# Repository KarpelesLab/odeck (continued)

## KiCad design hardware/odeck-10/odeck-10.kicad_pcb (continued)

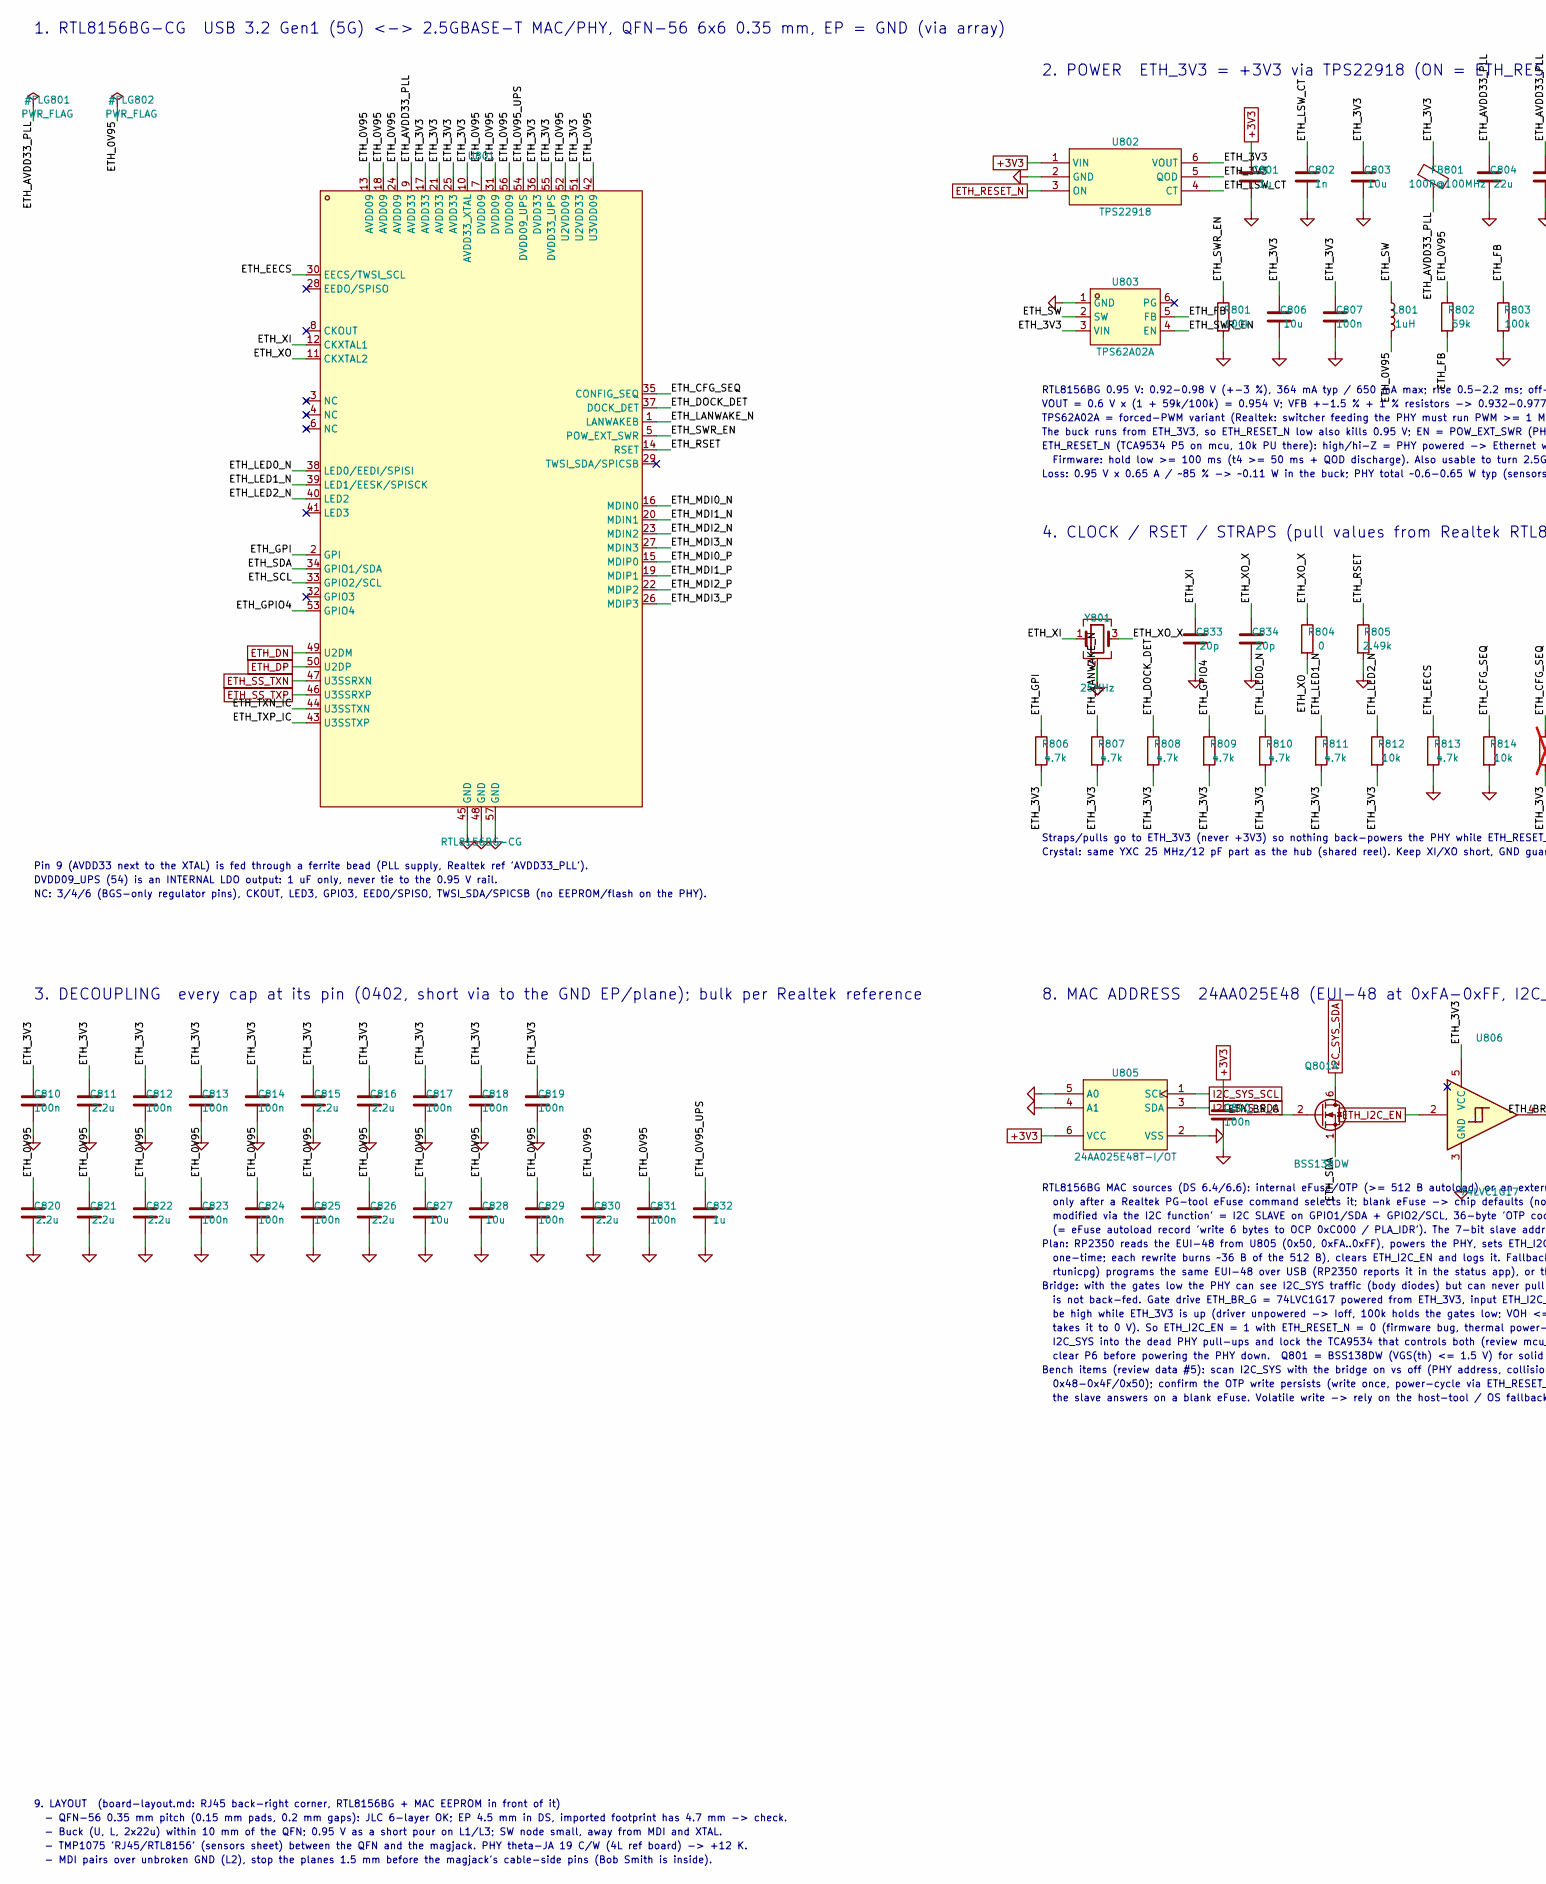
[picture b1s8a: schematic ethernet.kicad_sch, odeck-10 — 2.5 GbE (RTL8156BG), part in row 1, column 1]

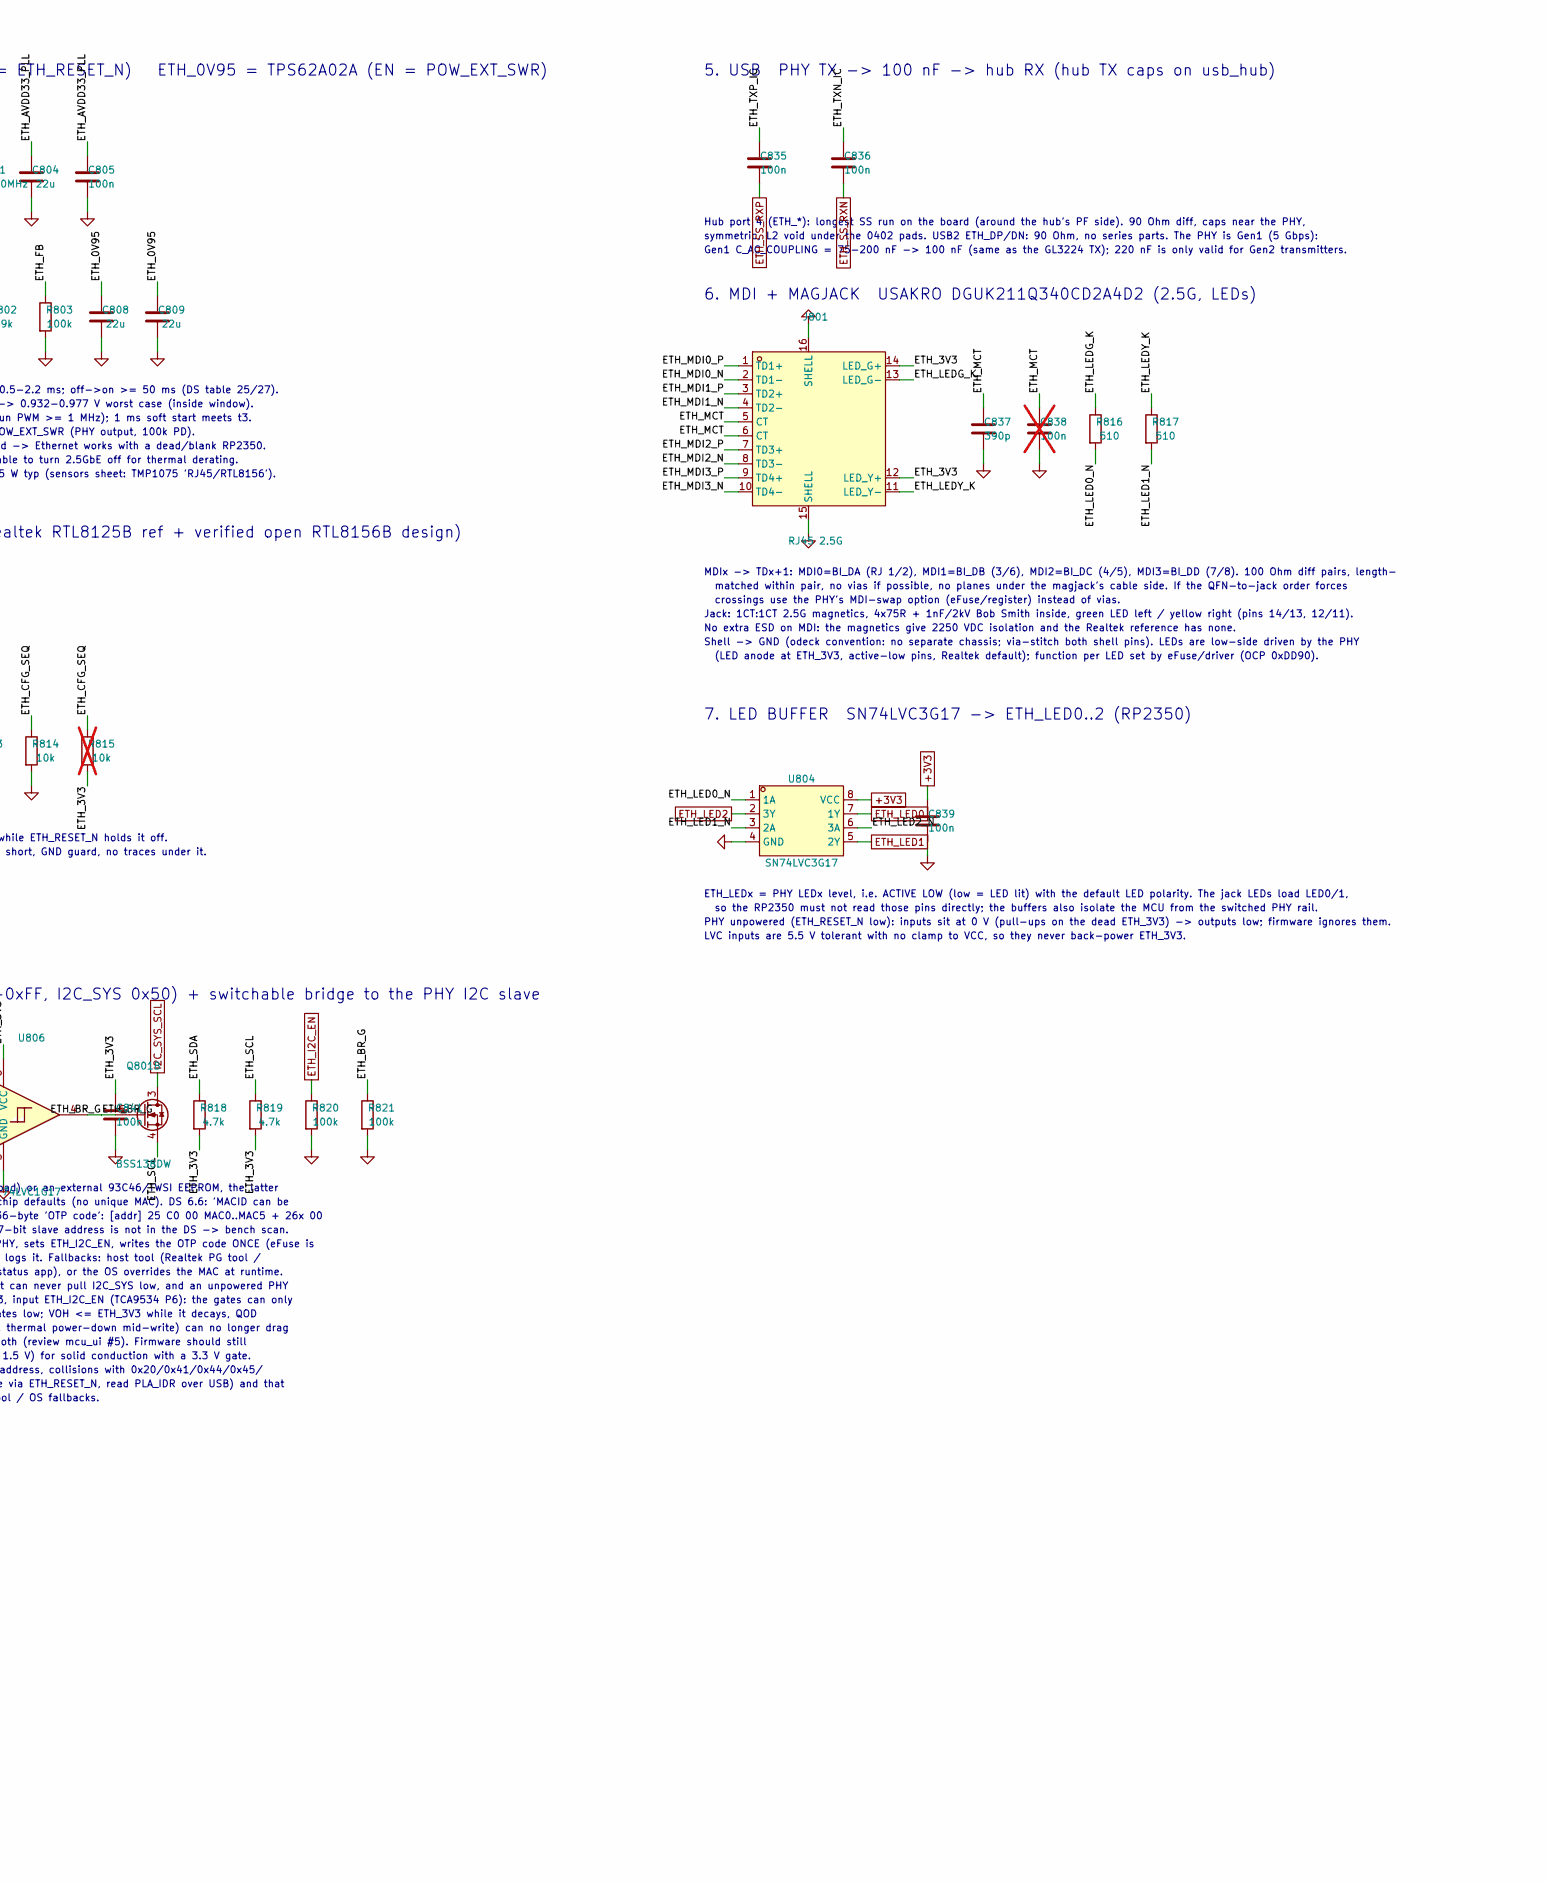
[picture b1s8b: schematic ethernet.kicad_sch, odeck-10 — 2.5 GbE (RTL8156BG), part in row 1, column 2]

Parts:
C801, C832: 1u; C_0402_1005Metric; LCSC C52923
C802: 1n; C_0402_1005Metric; LCSC C1523
C803, C806, C827, C828: 10u; C_0603_1608Metric; LCSC C19702
C804, C808, C809: 22u; C_0603_1608Metric; LCSC C59461
C805, C807, C810, C812, C813, C814, C817, C818, C819, C823, C824, C825, C829, C831, C835, C836, C839, C840, C841: 100n; C_0402_1005Metric; LCSC C1525
C811, C815, C816, C820, C821, C822, C826, C830: 2.2u; C_0402_1005Metric; LCSC C12530
C833, C834: 20p; C_0402_1005Metric; LCSC C1554
C837: 390p; C_0402_1005Metric; LCSC C282239
C838: 100n; C_0402_1005Metric; LCSC C1525; not fitted
FB801: 100R@100MHz; L_0805_2012Metric; LCSC C1015
J801: RJ45 2.5G; RJ45-TH_DGUK211Q340CD2A4D2; MPN DGUK211Q340CD2A4D2(2.5G); LCSC C19725134
L801: 1uH; L_Sunlord_SWPA4018S; LCSC C91250
Q801: BSS138DW; SOT-363_SC-70-6; MPN BSS138DW-7-F; LCSC C154900
R801, R803, R820, R821: 100k; R_0402_1005Metric; LCSC C25741
R802: 59k; R_0402_1005Metric; LCSC C32297
R804: 0; R_0402_1005Metric; LCSC C17168
R805: 2.49k; R_0402_1005Metric; LCSC C25884
R806, R807, R808, R809, R810, R811, R813, R818, R819: 4.7k; R_0402_1005Metric; LCSC C25900
R812, R814: 10k; R_0402_1005Metric; LCSC C25744
R815: 10k; R_0402_1005Metric; LCSC C25744; not fitted
R816, R817: 510; R_0402_1005Metric; LCSC C25123
U801: RTL8156BG-CG; QFN-56_L6.0-W6.0-P0.35--TL-EP4.7; MPN RTL8156BG-CG; LCSC C41376388
U802: TPS22918; SOT-23-6; MPN TPS22918DBVR; LCSC C131941
U803: TPS62A02A; SOT-5X3-6_W1.6-L1.2-P0.50-LS1.6-BL; MPN TPS62A02ADRLR; LCSC C5820994
U804: SN74LVC3G17; VSSOP-8_L2.1-W2.4-P0.50-LS3.2-BR; MPN SN74LVC3G17DCUR; LCSC C68245
U805: 24AA025E48T-I/OT; SOT-23-6; MPN 24AA025E48T-I/OT; LCSC C129895
U806: 74LVC1G17; SOT-23-5; MPN 74LVC1G17W5-7; LCSC C151394
Y801: 25MHz; Crystal_SMD_3225-4Pin_3.2x2.5mm; LCSC C9006

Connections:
+3V3: C801.1, C839.1, C840.1, U802.1 (VIN), U804.8 (VCC), U805.6 (VCC); also elsewhere on the board
/Ethernet/ETH_0V95: C808.1, C809.1, C820.1, C821.1, C822.1, C823.1, C824.1, C825.1, C826.1, C827.1, C828.1, C829.1, C830.1, C831.1, L801.2, R802.1, U801.7 (DVDD09), U801.13 (AVDD09), U801.18 (AVDD09), U801.24 (AVDD09), U801.31 (DVDD09), U801.42 (U3VDD09), U801.52 (U2VDD09), U801.56 (DVDD09)
/Ethernet/ETH_0V95_UPS: C832.1, U801.54 (DVDD09_UPS)
/Ethernet/ETH_3V3: C803.1, C806.1, C807.1, C810.1, C811.1, C812.1, C813.1, C814.1, C815.1, C816.1, C817.1, C818.1, C819.1, C841.1, FB801.1, J801.12 (LED_Y+), J801.14 (LED_G+), R806.2, R807.2, R808.2, R809.2, R810.2, R811.2, R812.2, R815.2, R818.2, R819.2, U801.10 (AVDD33_XTAL), U801.17 (AVDD33), U801.21 (AVDD33), U801.25 (AVDD33), U801.36 (DVDD33), U801.51 (U2VDD33), U801.55 (DVDD33_UPS), U802.5 (QOD), U802.6 (VOUT), U803.3 (VIN), U806.5 (VCC)
/Ethernet/ETH_AVDD33_PLL: C804.1, C805.1, FB801.2, U801.9 (AVDD33)
/Ethernet/ETH_BR_G: Q801.2 (G), Q801.5 (G), R821.1, U806.4
/Ethernet/ETH_CFG_SEQ: R814.1, R815.1, U801.35 (CONFIG_SEQ)
/Ethernet/ETH_DOCK_DET: R808.1, U801.37 (DOCK_DET)
/Ethernet/ETH_EECS: R813.1, U801.30 (EECS/TWSI_SCL)
/Ethernet/ETH_FB: R802.2, R803.1, U803.5 (FB)
/Ethernet/ETH_GPI: R806.1, U801.2 (GPI)
/Ethernet/ETH_GPIO4: R809.1, U801.53 (GPIO4)
/Ethernet/ETH_LANWAKE_N: R807.1, U801.1 (LANWAKEB)
/Ethernet/ETH_LED0_N: R810.1, R816.2, U801.38 (LED0/EEDI/SPISI), U804.1 (1A)
/Ethernet/ETH_LED1_N: R811.1, R817.2, U801.39 (LED1/EESK/SPISCK), U804.3 (2A)
/Ethernet/ETH_LED2_N: R812.1, U801.40 (LED2), U804.6 (3A)
/Ethernet/ETH_LEDG_K: J801.13 (LED_G-), R816.1
/Ethernet/ETH_LEDY_K: J801.11 (LED_Y-), R817.1
/Ethernet/ETH_LSW_CT: C802.1, U802.4 (CT)
/Ethernet/ETH_MCT: C837.1, C838.1, J801.5 (CT), J801.6 (CT)
/Ethernet/ETH_MDI0_N: J801.2 (TD1-), U801.16 (MDIN0)
/Ethernet/ETH_MDI0_P: J801.1 (TD1+), U801.15 (MDIP0)
/Ethernet/ETH_MDI1_N: J801.4 (TD2-), U801.20 (MDIN1)
/Ethernet/ETH_MDI1_P: J801.3 (TD2+), U801.19 (MDIP1)
/Ethernet/ETH_MDI2_N: J801.8 (TD3-), U801.23 (MDIN2)
/Ethernet/ETH_MDI2_P: J801.7 (TD3+), U801.22 (MDIP2)
/Ethernet/ETH_MDI3_N: J801.10 (TD4-), U801.27 (MDIN3)
/Ethernet/ETH_MDI3_P: J801.9 (TD4+), U801.26 (MDIP3)
/Ethernet/ETH_RSET: R805.1, U801.14 (RSET)
/Ethernet/ETH_SCL: Q801.4 (S), R819.1, U801.33 (GPIO2/SCL)
/Ethernet/ETH_SDA: Q801.1 (S), R818.1, U801.34 (GPIO1/SDA)
/Ethernet/ETH_SW: L801.1, U803.2 (SW)
/Ethernet/ETH_SWR_EN: R801.1, U801.5 (POW_EXT_SWR), U803.4 (EN)
/Ethernet/ETH_TXN_IC: C836.1, U801.44 (U3SSTXN)
/Ethernet/ETH_TXP_IC: C835.1, U801.43 (U3SSTXP)
/Ethernet/ETH_XI: C833.1, U801.12 (CKXTAL1), Y801.1
/Ethernet/ETH_XO: R804.2, U801.11 (CKXTAL2)
/Ethernet/ETH_XO_X: C834.1, R804.1, Y801.3
ETH_DN: U801.49 (U2DM); also elsewhere on the board
ETH_DP: U801.50 (U2DP); also elsewhere on the board
ETH_I2C_EN: R820.1, U806.2; also elsewhere on the board
ETH_LED0: U804.7 (1Y); also elsewhere on the board
ETH_LED1: U804.5 (2Y); also elsewhere on the board
ETH_LED2: U804.2 (3Y); also elsewhere on the board
ETH_RESET_N: U802.3 (ON); also elsewhere on the board
ETH_SS_RXN: C836.2; also elsewhere on the board
ETH_SS_RXP: C835.2; also elsewhere on the board
ETH_SS_TXN: U801.47 (U3SSRXN); also elsewhere on the board
ETH_SS_TXP: U801.46 (U3SSRXP); also elsewhere on the board
GND: C801.2, C802.2, C803.2, C804.2, C805.2, C806.2, C807.2, C808.2, C809.2, C810.2, C811.2, C812.2, C813.2, C814.2, C815.2, C816.2, C817.2, C818.2, C819.2, C820.2, C821.2, C822.2, C823.2, C824.2, C825.2, C826.2, C827.2, C828.2, C829.2, C830.2, C831.2, C832.2, C833.2, C834.2, C837.2, C838.2, C839.2, C840.2, C841.2, J801.15 (SHELL), J801.16 (SHELL), R801.2, R803.2, R805.2, R813.2, R814.2, R820.2, R821.2, U801.45 (GND), U801.48 (GND), U801.57 (GND), U802.2 (GND), U803.1 (GND), U804.4 (GND), U805.2 (VSS), U805.4 (A1), U805.5 (A0), U806.3 (GND), Y801.2 (G), Y801.4 (G); also elsewhere on the board
I2C_SYS_SCL: Q801.3 (D), U805.1 (SCL); also elsewhere on the board
I2C_SYS_SDA: Q801.6 (D), U805.3 (SDA); also elsewhere on the board

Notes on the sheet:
1. RTL8156BG-CG USB 3.2 Gen1 (5G) <-> 2.5GBASE-T MAC/PHY, QFN-56 6x6 0.35 mm, EP = GND (via array)
Pin 9 (AVDD33 next to the XTAL) is fed through a ferrite bead (PLL supply, Realtek ref 'AVDD33_PLL').
DVDD09_UPS (54) is an INTERNAL LDO output: 1 uF only, never tie to the 0.95 V rail.
NC: 3/4/6 (BGS-only regulator pins), CKOUT, LED3, GPIO3, EEDO/SPISO, TWSI_SDA/SPICSB (no EEPROM/flash on the PHY).
2. POWER ETH_3V3 = +3V3 via TPS22918 (ON = ETH_RESET_N) ETH_0V95 = TPS62A02A (EN = POW_EXT_SWR)
RTL8156BG 0.95 V: 0.92-0.98 V (+-3 %), 364 mA typ / 650 mA max; rise 0.5-2.2 ms; off->on >= 50 ms (DS table 25/27).
VOUT = 0.6 V x (1 + 59k/100k) = 0.954 V; VFB +-1.5 % + 1 % resistors -> 0.932-0.977 V worst case (inside window).
TPS62A02A = forced-PWM variant (Realtek: switcher feeding the PHY must run PWM >= 1 MHz); 1 ms soft start meets t3.
The buck runs from ETH_3V3, so ETH_RESET_N low also kills 0.95 V; EN = POW_EXT_SWR (PHY output, 100k PD).
ETH_RESET_N (TCA9534 P5 on mcu, 10k PU there): high/hi-Z = PHY powered -> Ethernet works with a dead/blank RP2350.
Firmware: hold low >= 100 ms (t4 >= 50 ms + QOD discharge). Also usable to turn 2.5GbE off for thermal derating.
Loss: 0.95 V x 0.65 A / ~85 % -> ~0.11 W in the buck; PHY total ~0.6-0.65 W typ (sensors sheet: TMP1075 'RJ45/RTL8156').
3. DECOUPLING every cap at its pin (0402, short via to the GND EP/plane); bulk per Realtek reference
4. CLOCK / RSET / STRAPS (pull values from Realtek RTL8125B ref + verified open RTL8156B design)
Straps/pulls go to ETH_3V3 (never +3V3) so nothing back-powers the PHY while ETH_RESET_N holds it off.
Crystal: same YXC 25 MHz/12 pF part as the hub (shared reel). Keep XI/XO short, GND guard, no traces under it.
5. USB PHY TX -> 100 nF -> hub RX (hub TX caps on usb_hub)
Hub port 4 (ETH_*): longest SS run on the board (around the hub's PF side). 90 Ohm diff, caps near the PHY,
symmetric, L2 void under the 0402 pads. USB2 ETH_DP/DN: 90 Ohm, no series parts. The PHY is Gen1 (5 Gbps):
Gen1 C_AC_COUPLING = 75-200 nF -> 100 nF (same as the GL3224 TX); 220 nF is only valid for Gen2 transmitters.
6. MDI + MAGJACK USAKRO DGUK211Q340CD2A4D2 (2.5G, LEDs)
MDIx -> TDx+1: MDI0=BI_DA (RJ 1/2), MDI1=BI_DB (3/6), MDI2=BI_DC (4/5), MDI3=BI_DD (7/8). 100 Ohm diff pairs, length-
matched within pair, no vias if possible, no planes under the magjack's cable side. If the QFN-to-jack order forces
crossings use the PHY's MDI-swap option (eFuse/register) instead of vias.
Jack: 1CT:1CT 2.5G magnetics, 4x75R + 1nF/2kV Bob Smith inside, green LED left / yellow right (pins 14/13, 12/11).
No extra ESD on MDI: the magnetics give 2250 VDC isolation and the Realtek reference has none.
Shell -> GND (odeck convention: no separate chassis; via-stitch both shell pins). LEDs are low-side driven by the PHY
(LED anode at ETH_3V3, active-low pins, Realtek default); function per LED set by eFuse/driver (OCP 0xDD90).
7. LED BUFFER SN74LVC3G17 -> ETH_LED0..2 (RP2350)
ETH_LEDx = PHY LEDx level, i.e. ACTIVE LOW (low = LED lit) with the default LED polarity. The jack LEDs load LED0/1,
so the RP2350 must not read those pins directly; the buffers also isolate the MCU from the switched PHY rail.
PHY unpowered (ETH_RESET_N low): inputs sit at 0 V (pull-ups on the dead ETH_3V3) -> outputs low; firmware ignores them.
LVC inputs are 5.5 V tolerant with no clamp to VCC, so they never back-power ETH_3V3.
8. MAC ADDRESS 24AA025E48 (EUI-48 at 0xFA-0xFF, I2C_SYS 0x50) + switchable bridge to the PHY I2C slave
RTL8156BG MAC sources (DS 6.4/6.6): internal eFuse/OTP (>= 512 B autoload) or an external 93C46/TWSI EEPROM, the latter
only after a Realtek PG-tool eFuse command selects it; blank eFuse -> chip defaults (no unique MAC). DS 6.6: 'MACID can be
modified via the I2C function' = I2C SLAVE on GPIO1/SDA + GPIO2/SCL, 36-byte 'OTP code': [addr] 25 C0 00 MAC0..MAC5 + 26x 00
(= eFuse autoload record 'write 6 bytes to OCP 0xC000 / PLA_IDR'). The 7-bit slave address is not in the DS -> bench scan.
Plan: RP2350 reads the EUI-48 from U805 (0x50, 0xFA..0xFF), powers the PHY, sets ETH_I2C_EN, writes the OTP code ONCE (eFuse is
one-time; each rewrite burns ~36 B of the 512 B), clears ETH_I2C_EN and logs it. Fallbacks: host tool (Realtek PG tool /

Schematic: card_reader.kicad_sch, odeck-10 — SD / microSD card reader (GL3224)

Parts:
C901: 10u; C_0805_2012Metric; LCSC C15850
C902, C905, C906, C907, C908, C914, C916, C917, C918: 100n; C_0402_1005Metric; LCSC C1525
C903: 10u; C_0603_1608Metric; LCSC C19702
C904, C910, C911, C912: 1u; C_0402_1005Metric; LCSC C52923
C909: 2.2u; C_0402_1005Metric; LCSC C12530
C913, C915: 4.7u; C_0402_1005Metric; LCSC C23733
C919, C920: 20p; C_0402_1005Metric; LCSC C1554
D901: green; LED_0805_2012Metric; LCSC C2297; not fitted
J901: SD-111; SD-SMD_SD-111; MPN SD-111; LCSC C410353
J902: DM3AT; SD-SMD_DM3AT-SF-PEJM5; MPN DM3AT-SF-PEJM5; LCSC C114218
R901: 680; R_0603_1608Metric; LCSC C23228
R902: 10k; R_0402_1005Metric; LCSC C25744
R903: 10k; R_0402_1005Metric; LCSC C25744; not fitted
R904, R905, R906: 1k; R_0402_1005Metric; LCSC C11702
R907: 1k; R_0402_1005Metric; LCSC C11702; not fitted
R908: 22; R_0402_1005Metric; LCSC C25092
U901: GL3224-ONY04; QFN-48_L7.0-W7.0-P0.50-BL-EP5.1; MPN GL3224-ONY04; LCSC C157358
Y901: 25MHz; Crystal_SMD_3225-4Pin_3.2x2.5mm; LCSC C9006

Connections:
+5V: C901.1, C902.1, U901.22 (VBUS); also elsewhere on the board
/Card reader/CR_1V2: C909.1, C910.1, U901.9 (AVDD12), U901.26 (DVDD12)
/Card reader/CR_3V3: C903.1, C904.1, C905.1, C906.1, C907.1, C908.1, R902.2, U901.6 (AVDD33), U901.15 (AVDD33), U901.25 (DVDD33), U901.34 (DVDD33), U901.44 (DVDD33)
/Card reader/CR_LED_A: D901.2 (A), R907.2
/Card reader/CR_LED_IC: R906.1, R907.1, U901.21 (LED)
/Card reader/CR_RTERM: R901.1, U901.16 (RTERM)
/Card reader/CR_SD_CDZ: J901.10 (CD), R904.1, U901.1 (SD1_CDZ)
/Card reader/CR_SD_CLK: J901.5 (CLK), U901.39 (S1CK_M1D0)
/Card reader/CR_SD_CMD: J901.2 (CMD), U901.40 (S1CM_M1D2)
/Card reader/CR_SD_D0: J901.7 (DAT0), U901.38 (S1D0_M1D1)
/Card reader/CR_SD_D1: J901.8 (DAT1), U901.37 (S1D1_M1BS)
/Card reader/CR_SD_D2: J901.9 (DAT2), U901.42 (S1D2_M1CK)
/Card reader/CR_SD_D3: J901.1 (CD/DAT3), U901.41 (S1D3_M1D3)
/Card reader/CR_SD_VCC: C913.1, C914.1, J901.4 (VDD), U901.23 (S1M1_VCC)
/Card reader/CR_SD_WP: J901.11 (WP), U901.2 (MS1_INS/SD1_WP)
/Card reader/CR_SPI_CK: R903.1, U901.19 (SPI_CK)
/Card reader/CR_SPI_MISO: R902.1, U901.17 (SPI_MISO)
/Card reader/CR_TXN_IC: C918.1, U901.7 (TXN)
/Card reader/CR_TXP_IC: C917.1, U901.8 (TXP)
/Card reader/CR_USD_CDZ: J902.9 (SW_B), R905.1, U901.35 (MS2_INS/SD2_WP), U901.36 (SD2_CDZ)
/Card reader/CR_USD_CLK: R908.1, U901.29 (S2CK_M2D0)
/Card reader/CR_USD_CLK_S: J902.5 (CLK), R908.2
/Card reader/CR_USD_CMD: J902.3 (CMD), U901.30 (S2CM_M2D2)
/Card reader/CR_USD_D0: J902.7 (DAT0), U901.28 (S2D0_M2D1)
/Card reader/CR_USD_D1: J902.8 (DAT1), U901.27 (S2D1_M2BS)
/Card reader/CR_USD_D2: J902.1 (DAT2), U901.32 (S2D2_M2CK)
/Card reader/CR_USD_D3: J902.2 (CD/DAT3), U901.31 (S2D3_M2D3)
/Card reader/CR_USD_VCC: C915.1, C916.1, J902.4 (VDD), U901.24 (S2M2_VCC)
/Card reader/CR_VUHS1: C911.1, U901.43 (VUHS_1)
/Card reader/CR_VUHS2: C912.1, U901.33 (VUHS_2)
/Card reader/CR_XI: C919.1, U901.13 (X1), Y901.1
/Card reader/CR_XO: C920.1, U901.14 (X2), Y901.3
CR_CD_SD_N: R904.2; also elsewhere on the board
CR_CD_USD_N: R905.2; also elsewhere on the board
CR_DN: U901.4 (DM); also elsewhere on the board
CR_DP: U901.5 (DP); also elsewhere on the board
CR_LED: R906.2; also elsewhere on the board
CR_SS_RXN: C918.2; also elsewhere on the board
CR_SS_RXP: C917.2; also elsewhere on the board
CR_SS_TXN: U901.10 (RXN); also elsewhere on the board
CR_SS_TXP: U901.11 (RXP); also elsewhere on the board
GND: C901.2, C902.2, C903.2, C904.2, C905.2, C906.2, C907.2, C908.2, C909.2, C910.2, C911.2, C912.2, C913.2, C914.2, C915.2, C916.2, C919.2, C920.2, D901.1 (K), J901.3 (VSS1), J901.6 (VSS2), J901.12 (EP), J901.13 (EP), J902.6 (VSS), J902.10, J902.11 (SW_A), J902.12, J902.13, J902.14, R901.2, R903.2, U901.3 (GND), U901.12 (GND), U901.49 (EP), Y901.2 (G), Y901.4 (G); also elsewhere on the board

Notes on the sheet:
1. GL3224-ONY04 USB 3.1 Gen1 (5 Gbps) 2-LUN card reader, QFN-48 7x7, EP = GND (via array)
2. POWER +5V -> VBUS; internal LDOs -> CR_3V3 (pin 25), CR_1V2 (pin 26)
VBUS = +5V (4.75-5.25 V). CR_3V3 / CR_1V2 are the GL3224's own LDO outputs: never tie them to +3V3 or any other rail.
Genesys GL3224(E) demo board V3.00 + open GL3224 designs: VBUS 2.2-10 uF, DVDD33 2.2-10 uF, AVDD33/DVDD33 pins 0.1-1 uF, AVDD12 2.2 uF,
DVDD12 1 uF, VUHS 0.1-1 uF, card VCC up to 10 uF. Card power is switched by the GL3224's on-chip FETs (S1M1_VCC / S2M2_VCC);
card VCC kept at 4.7 uF + 100 nF so the internal 3.3 V LDO is not dipped at card power-on (proven designs use up to 10 uF).
Budget: GL3224 147 mA (SS U0 active) + up to ~200 mA per UHS-I card, all through the internal 5->3.3 V LDO:
~(5.1-3.3) V x 0.35 A = 0.63 W in the QFN (theta-JA 33 C/W -> +21 K). Thermal pad via array to inner GND planes.
3. USB / CLOCK / RTERM / ROM OPTIONS
Hub link: CR_SS_TX* = hub transmits (220 nF on usb_hub) -> GL3224 RXP/RXN direct. GL3224 TXP/TXN -> 100 nF here -> CR_SS_RX* -> hub.
GL3224 is USB 3.1 Gen1: hub port 1 trains at 5 Gbps (~400 MB/s) - well above UHS-I SDR104 (104 MB/s).
Gen1 transmitter AC cap range is 75-200 nF, so 100 nF here (the 220 nF Gen2 value is out of range for a Gen1 TX).
No reset pin: internal POR. Boots from ROM (no SPI flash). SPI_CS / SPI_MOSI NC, S1D4-7 NC (MMC 8-bit only).
Crystal: GL3224 accepts 25 MHz +-0.03 %; same YXC 3225 part as the hub (JLC basic).
4. CARD SOCKETS slot 1 = full-size SD (S1*), slot 2 = microSD (S2*). Both push-push.
SD-111 (Hanbo drawing): CD switch to pin 3 VSS1 closes with a card; WP switch to GND closes when the card is UNLOCKED, open when
locked or no card -> GL3224 SD1_WP (46k internal pull-up): 0 = write enable, 1 = write protect. Matches directly, no inverter.
Pin 2 is MS1_INS/SD1_WP: with no card the WP switch is open (high) so no false Memory Stick insert is seen.
DM3AT: normally-open detect switch SW_A (GND) - SW_B (CDZ). Pin 35 MS2_INS/SD2_WP is tied to CR_USD_CDZ (NOT GND): it is also
the Memory Stick insert input (0 = MS inserted). No card: CDZ high -> no MS, no WP. Card: low -> SD present, write enabled
(same state as slot 1 with an unlocked SD). Two 46k internal pull-ups in parallel on the node (~23k) - fine.
Bench item: the ROM must give SDx_CDZ = 0 priority over MSx_INS = 0 (DS silent) - unlocked SD in each slot enumerates
as writable SD, not MS. If not: inverter/strap, ask Genesys FAE.
CMD / DAT0-3 pull-ups: GL3224 internal 15k (DS table 5.3) -> no external resistors. Route each slot's CLK/CMD/DAT as a
50 Ohm group, length-matched +-1 mm, CLK with GND guard (SDR104 = 208 MHz), keep stubs to zero.
5. CARD DETECT -> TCA9534 P3/P4, ACTIVITY -> RP2350 (read-only)
The GL3224 needs the card-detect switches itself (SD1_CDZ / SD2_CDZ, 46k internal pull-up to CR_3V3, low = card).
The TCA9534 (mcu, P3/P4) taps the same nodes through 1k: input only, no internal pulls (TCA9534 DS 8), 5 V tolerant.
1k limits current if the pin is ever mis-configured as output. CR_3V3 exists whenever +5V does, and +3V3 is derived
from +5V, so the expander never sees the node while unpowered in a way that back-feeds the GL3224.
CR_USD_CDZ also drives GL3224 pin 35 (MS2_INS/SD2_WP), see section 4.
CR_LED: GL3224 LED output (push-pull 3.3 V, active high = access), 1k to the RP2350 GPIO (firmware shows activity on the LCD).

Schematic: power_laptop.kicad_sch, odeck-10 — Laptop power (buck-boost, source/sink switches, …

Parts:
C201, C202, C203, C204: 4.7u/100V; C_1210_3225Metric; LCSC C697607
C205, C206, C207, C208, C209, C210, C233: 10u/50V; C_1210_3225Metric; LCSC C432929
C211, C212: 100u/35V; CP_Elec_6.3x7.7; LCSC C2982822
C213, C219, C220, C228, C229, C234, C235, C236, C237: 100n/50V; C_0603_1608Metric; LCSC C14663
C214: 100n/100V; C_0805_2012Metric; LCSC C28233
C215: 1u/100V; C_0805_2012Metric; LCSC C126585
C216, C238: 1u/50V; C_0603_1608Metric; LCSC C15849
C217, C218: 22u; C_0805_2012Metric; LCSC C45783
C221: 100p; C_0402_1005Metric; LCSC C1546
C222: 22n; C_0402_1005Metric; LCSC C1532
C223: 6.8n; C_0603_1608Metric; LCSC C1631
C224: 82p; C_0402_1005Metric; LCSC C45501
C225, C240: 1n; C_0402_1005Metric; LCSC C1523
C226: 4.7u; C_0603_1608Metric; LCSC C19666
C227: 4.7n; C_0402_1005Metric; LCSC C1538
C230: 22n/50V; C_0603_1608Metric; LCSC C21122
C231, C232, C242, C244: 100n; C_0402_1005Metric; LCSC C1525
C239: 3.3n; C_0603_1608Metric; LCSC C1613
C241: 10u; C_0805_2012Metric; LCSC C15850
C243: 2.2n; C_0603_1608Metric; LCSC C1604
D201, D206: 1N4148W; D_SOD-123; LCSC C81598
D202: BZT52C5V1; D_SOD-123; LCSC C173407
D203: BAT54A; SOT-23; LCSC C130910
D204: BAT46W; D_SOD-123; LCSC C83152
D205: BAV70; SOT-23; LCSC C68978
L201: 10u; IND-SMD_L11.3-W10.0_XAL1010-332ME; MPN XAL1010-103MED; LCSC C6358489
Q201, Q202: BSC0805LS; PG-TDSON-8_L5.2-W5.9-P1.27-LS6.2-BL-EP; MPN BSC0805LS; LCSC C534374
Q203, Q204, Q217: CSD18543Q3A; VSONP-8_L3.1-W3.1-P0.65-LS3.5-BL; MPN CSD18543Q3A; LCSC C840100
Q205, Q206, Q207, Q208, Q209, Q210, Q211, Q215, Q216, Q218, Q219, Q220, Q221: AO3400A; SOT-23; LCSC C20917
Q212: 2N7002; SOT-23; LCSC C8545
Q213, Q214: BSC026N08NS5; PG-TDSON-8_L5.0-W6.0-P1.27-BL-EP; MPN BSC026N08NS5ATMA1; LCSC C5955453
R201: 4m; R_2512_6332Metric; MPN RLP25FEGR004; LCSC C459681
R202: 8m; R_2512_6332Metric; MPN PE2512FKE070R008L; LCSC C2075410
R203, R204, R205, R206, R217: 0; R_0402_1005Metric; LCSC C17168
R207: 200k; R_0805_2012Metric; LCSC C17539
R208: 43k; R_0402_1005Metric; LCSC C8329
R209: 10; R_0603_1608Metric; LCSC C22859
R210, R211: 10; R_0402_1005Metric; LCSC C25077
R212: 86.6k; R_0402_1005Metric; LCSC C48533697
R213, R220, R225, R228, R231, R232, R239, R241, R242, R245, R251: 100k; R_0402_1005Metric; LCSC C25741
R214: 6.49k; R_0402_1005Metric; LCSC C2998055
R215: 62k; R_0402_1005Metric; LCSC C2909375
R216, R219, R237, R240, R249, R252, R256, R258: 10k; R_0402_1005Metric; LCSC C25744
R218: 0; R_0402_1005Metric; LCSC C17168; not fitted
R221, R223: 24.3k; R_0402_1005Metric; LCSC C26969
R222: 1.5k; R_0402_1005Metric; LCSC C25867
R224, R227, R230, R250: 1k; R_0402_1005Metric; LCSC C11702
R226: 8.66k; R_0402_1005Metric; LCSC C5126133
R229: 5.23k; R_0402_1005Metric; LCSC C2933105
R233: 1M; R_0402_1005Metric; LCSC C26083
R234: 470k; R_0805_2012Metric; LCSC C17709
R235: 150; R_2512_6332Metric; LCSC C2934049
R236: 255k; R_0402_1005Metric; LCSC C270623
R238: 100; R_0402_1005Metric; LCSC C25076
R243: 5m; R_1206_3216Metric; MPN RLM12FTCMR005; LCSC C316225
R244: 422k; R_0402_1005Metric; LCSC C477738
R246: 121k; R_0402_1005Metric; LCSC C11693
R247, R253: 47k; R_0402_1005Metric; LCSC C25792
R248: 40.2k; R_0402_1005Metric; LCSC C25893
R254: 1.1M; R_0402_1005Metric; LCSC C133039
R255: 46.4k; R_0402_1005Metric; LCSC C5126026
R257: 4.7k; R_0402_1005Metric; LCSC C25900
U201: LM51770; HTSSOP-38_L9.7-W4.4-P0.50-LS6.4-BL-EP; MPN LM51770DCPR; LCSC C43351171
U202: LM74800-Q1; WSON-12_L3.0-W3.0-P0.50-TL-EP-2; MPN LM74800QDRRRQ1; LCSC C3215600
U203: SN74LVC1G11; SOT-23-6; LCSC C22046
U204: INA226; MSOP-10_L3.0-W3.0-P0.50-LS5.0-BL; MPN INA226AIDGSR; LCSC C49851
U205: LM74502; SOT-23-8_L2.9-W1.6-P0.65-LS2.8-BL; MPN LM74502DDFR; LCSC C3236215
U206: TPS259470A; VQFN-10_L2.0-W2.0-P0.45-TL; MPN TPS259470ARPWR; LCSC C3662799
U207: TLV3011; SOT-23-6_L2.9-W1.6-P0.95-LS2.8-BR; MPN TLV3011AIDBVR; LCSC C2870632

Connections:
+3V3: C231.1, C232.1, C244.1, R219.2, R240.2, R242.2, R258.2, U203.5 (VCC), U204.1 (A1), U204.6 (VS+), U207.6 (VCC); also elsewhere on the board
+5V: C241.1, U206.6 (OUT); also elsewhere on the board
/Laptop power out/BB_BIAS: C216.1, R209.2, U201.1 (BIAS)
/Laptop power out/BB_CFG: R214.1, U201.13 (CFG)
/Laptop power out/BB_COMP: C224.1, R215.1, U201.18 (COMP)
/Laptop power out/BB_COMPZ: C223.1, R215.2
/Laptop power out/BB_CSA: C221.1, R210.2, U201.37 (CSA)
/Laptop power out/BB_CSB: C221.2, R211.2, U201.38 (CSB)
/Laptop power out/BB_DIS: Q212.3 (D), R235.2
/Laptop power out/BB_EN: Q209.3 (D), R207.2, R208.1, U201.4 (EN/UVLO)
/Laptop power out/BB_ENKILL: D201.2 (A), D202.1 (K), Q209.1 (G), Q210.3 (D), Q212.1 (G), R233.2, R234.2
/Laptop power out/BB_ENS: Q210.2 (S), Q211.3 (D)
/Laptop power out/BB_FB: R220.2, R221.1, R222.1, U201.19 (FB)
/Laptop power out/BB_FBM: C226.1, R222.2, R223.1, R226.1, R229.1
/Laptop power out/BB_G1: Q201.4 (G), R203.2
/Laptop power out/BB_G2: Q202.4 (G), R204.2
/Laptop power out/BB_G3: Q203.4 (G), R205.2
/Laptop power out/BB_G4: Q204.4 (G), R206.2
/Laptop power out/BB_HB1: C219.1, U201.35 (HB1)
/Laptop power out/BB_HB2: C220.1, U201.26 (HB2)
/Laptop power out/BB_HO1: R203.1, U201.34 (HO1)
/Laptop power out/BB_HO2: R206.1, U201.27 (HO2)
/Laptop power out/BB_IMON: R216.1, U201.6 (IMONOUT)
/Laptop power out/BB_IMONZ: C225.1, R216.2
/Laptop power out/BB_LO1: R204.1, U201.32 (LO1)
/Laptop power out/BB_LO2: R205.1, U201.29 (LO2)
/Laptop power out/BB_LS: L201.1, R201.2, R211.1
/Laptop power out/BB_MODE: R217.1, R218.1, U201.12 (MODE)
/Laptop power out/BB_PGH: C227.1, D201.1 (K), Q208.1 (G), R233.1
/Laptop power out/BB_PSO: C205.1, C206.1, C207.1, C208.1, Q204.5 (D), Q204.6 (D), Q204.7 (D), Q204.8 (D), Q204.9 (D), R202.1, U201.23 (ISNSP)
/Laptop power out/BB_RT: R212.1, U201.15 (RT)
/Laptop power out/BB_SLOPE: R213.1, U201.14 (SLOPE)
/Laptop power out/BB_SS: C222.1, U201.16 (SS/ATRK)
/Laptop power out/BB_SW1: C219.2, Q201.1 (S), Q201.2 (S), Q201.3 (S), Q202.5 (D), Q202.6 (D), Q202.7 (D), Q202.8 (D), Q202.9 (EP), R201.1, R210.1, U201.36 (SW1)
/Laptop power out/BB_SW2: C220.2, L201.2, Q203.5 (D), Q203.6 (D), Q203.7 (D), Q203.8 (D), Q203.9 (D), Q204.1 (S), Q204.2 (S), Q204.3 (S), U201.25 (SW2)
/Laptop power out/BB_VCC: C217.1, C218.1, R218.2, U201.11 (SYNC), U201.31 (VCC)
/Laptop power out/BB_VS0D: Q205.3 (D), R223.2
/Laptop power out/BB_VS0G: Q205.1 (G), R224.2
/Laptop power out/BB_VS1D: Q206.3 (D), R226.2
/Laptop power out/BB_VS1G: Q206.1 (G), R227.2
/Laptop power out/BB_VS2D: Q207.3 (D), R229.2
/Laptop power out/BB_VS2G: Q207.1 (G), R230.2
/Laptop power out/OVP_DIV: C243.1, R254.2, R255.1, R257.2, U207.3 (IN+)
/Laptop power out/OVP_FB: D206.1 (K), R257.1
/Laptop power out/OVP_REF: U207.4 (IN-), U207.5 (REF)
/Laptop power out/OVP_TOP: D205.3 (K), R254.1
/Laptop power out/OVP_TRIP: D206.2 (A), Q221.1 (G), R256.1, U207.1 (OUT)
/Laptop power out/SNK_DVDT: C239.1, U206.7 (DVDT)
/Laptop power out/SNK_GATE: Q217.4 (G), U205.6 (GATE)
/Laptop power out/SNK_ILM: R250.1, U206.9 (ILM)
/Laptop power out/SNK_ITIMER: C240.1, U206.10 (ITIMER)
/Laptop power out/SNK_KX: Q218.2 (S), Q219.3 (D)
/Laptop power out/SNK_MID: C238.1, Q217.1 (S), Q217.2 (S), Q217.3 (S), R246.1, R248.1, U205.8 (SRC), U206.5 (IN)
/Laptop power out/SNK_ON: Q218.3 (D), Q220.3 (D), R252.2, R253.1, U205.1 (EN/UVLO)
/Laptop power out/SNK_OV: R244.2, R245.1, U205.7 (OV)
/Laptop power out/SNK_OVLO: R248.2, R249.1, U206.2 (OVLO/OVCSEL)
/Laptop power out/SNK_PGD: C242.1, D204.2 (A), Q215.1 (G), Q219.1 (G), R251.2
/Laptop power out/SNK_UV: R246.2, R247.1, U206.1 (EN/UVLO)
/Laptop power out/SNK_VCAP: C237.1, U205.4 (VCAP)
/Laptop power out/SRC_CAP: C229.1, U202.11 (CAP)
/Laptop power out/SRC_DGATE: Q213.4 (G), U202.1 (DGATE)
/Laptop power out/SRC_DVDT: C230.1, R238.2
/Laptop power out/SRC_HGATE: Q214.4 (G), R238.1, U202.8 (HGATE)
/Laptop power out/SRC_MID: C228.1, C229.2, Q213.5 (D), Q213.6 (D), Q213.7 (D), Q213.8 (D), Q214.5 (D), Q214.6 (D), Q214.7 (D), Q214.8 (D), U202.10 (VS), U202.12 (C)
/Laptop power out/SRC_ON: Q220.1 (G), R239.1, U202.6 (EN/UVLO), U203.4
/Laptop power out/SRC_OV: R236.2, R237.1, U202.5 (OV)
/Laptop power out/SRC_OVT: R236.1, U202.4 (SW)
/Laptop power out/SRC_PG5N: Q215.3 (D), Q216.1 (G), R242.1
/Laptop power out/SRC_PGOK: D203.3, Q216.3 (D), R240.1, U203.6
EXT_PWR_PRESENT: Q218.1 (G), U203.3; also elsewhere on the board
GND: C201.2, C202.2, C203.2, C204.2, C205.2, C206.2, C207.2, C208.2, C209.2, C210.2, C211.2, C212.2, C213.2, C214.2, C215.2, C216.2, C217.2, C218.2, C222.2, C223.2, C224.2, C225.2, C226.2, C227.2, C228.2, C230.2, C231.2, C232.2, C233.2, C234.2, C235.2, C236.2, C238.2, C239.2, C240.2, C241.2, C242.2, C243.2, C244.2, D202.2 (A), Q202.1 (S), Q202.2 (S), Q202.3 (S), Q203.1 (S), Q203.2 (S), Q203.3 (S), Q205.2 (S), Q206.2 (S), Q207.2 (S), Q208.2 (S), Q209.2 (S), Q211.2 (S), Q212.2 (S), Q215.2 (S), Q216.2 (S), Q219.2 (S), Q220.2 (S), Q221.2 (S), R208.2, R212.2, R213.2, R214.2, R217.2, R221.2, R225.2, R228.2, R231.2, R232.2, R237.2, R239.2, R241.2, R245.2, R247.2, R249.2, R250.2, R253.2, R255.2, U201.10 (DTRK), U201.17 (AGND), U201.30 (PGND), U201.39 (EP), U202.7 (GND), U203.2 (GND), U204.2 (A0), U204.7 (GND), U205.2 (GND), U206.8 (GND), U207.2 (GND); also elsewhere on the board
I2C_SYS_SCL: U204.5 (SCL); also elsewhere on the board
I2C_SYS_SDA: U204.4 (SDA); also elsewhere on the board
LAPTOP_OVP_N: D203.2, Q211.1 (G), Q221.3 (D), R258.1; also elsewhere on the board
LAPTOP_SNK_EN: R252.1; also elsewhere on the board
LAPTOP_SRC_EN: R241.1, U203.1; also elsewhere on the board
PG_5V: D204.1 (K), R251.1; also elsewhere on the board
VBB_EN: Q210.1 (G), R232.1, R256.2; also elsewhere on the board
VBB_OUT: C209.1, C210.1, C211.1, C212.1, C213.1, D205.2 (A), Q213.1 (S), Q213.2 (S), Q213.3 (S), R202.2, R209.1, R220.1, R235.1, U201.20 (VOUT), U201.22 (ISNSN), U202.2 (A)
VBB_PG: D203.1, Q208.3 (D), R219.1, U201.7 (nFLT); also elsewhere on the board
VBB_VSEL0: R224.1, R225.1; also elsewhere on the board
VBB_VSEL1: R227.1, R228.1; also elsewhere on the board
VBB_VSEL2: R230.1, R231.1; also elsewhere on the board
VBUS_LAPTOP: C233.1, C234.1, D205.1 (A), R243.2, U202.3 (VSNS), U204.8 (VBUS), U204.9 (VIN-); also elsewhere on the board
VBUS_LSW: C235.1, C236.1, C237.2, Q214.1 (S), Q214.2 (S), Q214.3 (S), Q217.5 (D), Q217.6 (D), Q217.7 (D), Q217.8 (D), Q217.9 (D), R243.1, R244.1, U202.9 (OUT), U204.10 (VIN+), U205.5 (VS); also elsewhere on the board
VIN: C201.1, C202.1, C203.1, C204.1, C214.1, C215.1, Q201.5 (D), Q201.6 (D), Q201.7 (D), Q201.8 (D), Q201.9 (EP), R207.1, R234.1, U201.3 (VIN); also elsewhere on the board

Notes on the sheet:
1. LM51770 4-SWITCH BUCK-BOOST POWER STAGE VIN 9-50 V -> VBB_OUT 5.1/9/15/20/28 V, 5 A (140 W) fsw = 347 kHz (RT 86.6k). L = Coilcraft XAL1010-103 10 uH (Isat 17.5 A, 14.75 mOhm max). Ripple: 3.4 A p-p worst (48 V -> 28 V buck), 2.0 A (14 V -> 28 V boost). Input half-bridge: 2x BSC0805LS (100 V, 7.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
2. LM51770 CONTROLLER BIAS from VBB_OUT (10 R/1 uF): VCC LDO runs from min(VIN, VBB_OUT) above 6.5 V -> less LDO loss at 48 V in. EN/UVLO: 200k/43k from VIN -> on at 8.1 V, off at 6.8 V (5 uA hysteresis current). Q pulls EN/UVLO low unless VBB_EN AND LAPTOP_OVP_N (see section 3). CFG 6.49k = R2D #7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
3. OUTPUT VOLTAGE SELECT (PMG1 GPIOs only; RP2350 has no path here) VOUT = 1 V x (1 + Rtop x Gfb). Rtop 100k, Rbot 24.3k -> 5.115 V with all VSEL low (default, no firmware). Switched branches hang off node BB_FBM, which connects to FB through Rs = 1.5k and is held by Cm = 4.7 uF: any VSEL change (e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
4. LAPTOP SOURCE SWITCH VBB_OUT -> VBUS_LSW -> 5 mOhm -> VBUS_LAPTOP LM74800-Q1: Q (DGATE) = ideal diode (blocks laptop -> VBB_OUT in < 1 us), Q (HGATE) = on/off, common drain, 2x BSC026N08NS5 (80 V, 2.6 mOhm @10 V; same FET as power_input): 5 A -> 0.13 W total. HARDWARE ENABLE: SRC_ON = LAPTOP_SRC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
5. VBUS_LAPTOP MONITOR + CAPACITANCE INA226 on I2C_SYS at 0x44 (A1 = VS, A0 = GND). Shunt 5 mOhm (WSL2512): 5 A -> 25 mV of +-81.92 mV, 0.125 W. Bidirectional: + = sourcing to laptop, - = bus-powered sink. CURRENT_LSB 0.5 mA -> CAL = 2048. VBUS pin on the connector side (36 V max > 32.6 V backstop)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
6. BUS-POWER SINK SWITCH VBUS_LSW -> SNK_MID -> +5V (only without external power) Stage 1, 60 V blocking: CSD18543Q3A driven by LM74502 (charge pump, 3.2-65 V). Off -> blocks up to 60 V (VBUS is 28 V when we source); body diode points back to VBUS, reverse handled by stage 2. OV cut-off 422k/100k -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
7. INDEPENDENT VBUS OVP (latched) -> LAPTOP_OVP_N Senses max(VBUS_LAPTOP, VBB_OUT) through BAV70 (100 V): also catches a run-away buck-boost before the source switch closes. 1.1M/46.4k + 0.45 V diode: trip = 1.242 x 24.7 + 0.45 = 31.1 V (~29.9-32.3 V RSS, 29.3-33.1 V all corners) > 28.7 V max regul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
